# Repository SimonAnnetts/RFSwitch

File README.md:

# RFSwitch

A 4-way RF switch (one input, four selectable outputs OR four selectable inputs and one output) built from conventional through-hole parts from my parts bin: **J310 JFETs**, a **CD4104-style quad low-to-high voltage level translator**, and a handful of resistors and capacitors.

The RF path is switched at 9–12 V, but the channel-select lines are plain 3.3 V
logic, so the board can be driven directly from a Raspberry Pi Pico W (or any
3.3 V source).

* KiCad project: [RFSwitch/RFSwitch.kicad_pro](RFSwitch/RFSwitch.kicad_pro)
* Schematic: [RFSwitch/RFSwitch.kicad_sch](RFSwitch/RFSwitch.kicad_sch)
* PCB: [RFSwitch/RFSwitch.kicad_pcb](RFSwitch/RFSwitch.kicad_pcb)
* Symbols, footprints and 3D models used by the project are in `RFSwitch/libs` and `RFSwitch/packages3D`.

The switch should work at least up to 75Mhz, and probably well into the VHF range, but I have not tested it yet.

10 PCBs were ordered from JLCPCB in November 2026 costing about GBP 5.00 in total with shipping included. The boards are 50 mm × 50 mm, two-layer, ENIG finish, with a solder mask and silkscreen. I await their arrival, and once I have built and tested one, I will update this README with measured performance figures.

## Interfaces

### Control header J1 (1x8, 2.54 mm)

| Pin | Signal     | Description                                              |
|-----|------------|----------------------------------------------------------|
| 1   | GND        | Ground                                                   |
| 2   | VCC        | 9–12 V supply for the FET bias and switching             |
| 3   | +3V3       | 3.3 V logic supply (from the Pico's 3V3 out)             |
| 4   | EN         | Enables the level-shifter outputs                        |
| 5   | RF1_SEL    | Select channel 1 (3.3 V logic)                           |
| 6   | RF2_SEL    | Select channel 2                                         |
| 7   | RF3_SEL    | Select channel 3                                         |
| 8   | RF4_SEL    | Select channel 4                                         |

### RF connectors

Five edge-mount SMA connectors: `RFIN` (common) and `RFOUT1` … `RFOUT4`.

## How it works

### 1. Signal path

```
                       RF5 (common node, DC-biased to VCC via R18 10k)
                        │
 RFIN ──L1──C4(100n)────┤
                        ├── Q1 (series J310) ── RF1 ──C9(100n)──┬── RFOUT1
                        │                         │             C13 2.2p to GND
                        │                    Q5 (shunt J310)
                        │                         │
                        │                 "Net-(Q5-S)" node ── R19 10k to VCC
                        │                         │             C5..C8 100n to GND
                        ├── Q2 ── RF2 ── (Q6 shunt) ... C10 ── RFOUT2
                        ├── Q3 ── RF3 ── (Q7 shunt) ... C11 ── RFOUT3
                        └── Q4 ── RF4 ── (Q8 shunt) ... C12 ── RFOUT4
```

Each channel has two J310 JFETs:

| Channel | Series FET (common ↔ channel) | Shunt FET (channel ↔ RF ground) |
|---------|-------------------------------|---------------------------------|
| 1       | Q1                            | Q5                              |
| 2       | Q2                            | Q6                              |
| 3       | Q3                            | Q7                              |
| 4       | Q4                            | Q8                              |

* The **series** FET connects the common node `RF5` to the channel node
  (`RF1`…`RF4`). When it is on, the signal passes through; when it is off, the
  channel is disconnected.
* The **shunt** FET connects the channel node to the shunt-source net
  (`Net-(Q5-S)`). That net is held at VCC by R19 (10 k) and decoupled to ground
  by C5–C8 (100 nF), so it is an **RF ground**. When the shunt FET is on it
  shorts any leakage from an unselected channel to ground, which improves
  off-channel isolation.
* `RFIN` reaches the common node through L1 and the DC-blocking capacitor C4;
  each output has its own DC-blocking capacitor (C9–C12, 100 nF).

### 2. Why a J310 can be a switch here

A J310 is a depletion-mode N-channel JFET: with V<sub>GS</sub> = 0 V it is fully
**on** (low channel resistance), and it turns **off** when the gate is taken
several volts below the source (pinch-off is roughly −2 to −6 V).

The schematic takes advantage of this by putting the whole RF path at a **DC
level of VCC**:

* `RF5` is pulled to VCC through R18 (10 k).
* The shunt-source net is pulled to VCC through R19 (10 k).
* Because a channel node is always connected either to `RF5` (series FET on) or
  to the shunt-source net (shunt FET on), every FET source and drain sits at
  about VCC in DC terms.
* The C4 and C9–C12 capacitors block that DC from the connectors.

The FET gates are then driven between **VCC** and **0 V**:

* Gate = VCC → V<sub>GS</sub> = 0 V → FET **on**.
* Gate = 0 V → V<sub>GS</sub> ≈ −VCC (−9 to −12 V) → FET firmly **off**.

Pinching off with the full supply (far beyond pinch-off voltage) keeps the
off-FETs well clear of conduction on RF signal peaks. This is why the board
wants a 9 V or 12 V supply rather than 3.3 V: a 3.3 V gate swing could not
reliably pinch off a J310.

### 3. Level shifting with the 4104

U1 is a quad low-voltage to high-voltage translator with tri-state outputs. It
is supplied from two rails:

| Pin | Name  | Connection                                                   |
|-----|-------|--------------------------------------------------------------|
| 1   | Vddo  | `VCC` (9–12 V) – output side supply                          |
| 16  | Vddi  | `VDDi` – 3.3 V through R1 (1 k), decoupled by C1 (100 nF)    |
| 8   | Vss   | GND                                                          |
| 15  | EN    | `EN` from J1                                                 |

Each of the four sections has one 3.3 V input (`RFn_SEL`) and **two** outputs at
VCC level: a "true" output `RFn_T` and a complementary output `RFn_S`.

| Section | Input (U1 pin) | `_T` output (pin) | `_S` output (pin) |
|---------|----------------|-------------------|-------------------|
| 1       | RF1_SEL (4)    | RF1_T (3)         | RF1_S (2)         |
| 2       | RF2_SEL (12)   | RF2_T (13)        | RF2_S (14)        |
| 3       | RF3_SEL (11)   | RF3_T (10)        | RF3_S (9)         |
| 4       | RF4_SEL (5)    | RF4_T (6)         | RF4_S (7)         |

Each output reaches its FET gate through a 15 k resistor (R10–R17). The `_T`
output drives the **series** FET and the `_S` output drives the **shunt** FET:

| Series FET | Gate net | Shunt FET | Gate net |
|------------|----------|-----------|----------|
| Q1 | RF1_T via R10 | Q5 | RF1_S via R11 |
| Q2 | RF2_T via R12 | Q6 | RF2_S via R13 |
| Q3 | RF3_T via R14 | Q7 | RF3_S via R15 |
| Q4 | RF4_T via R16 | Q8 | RF4_S via R17 |

### 4. Truth table

Because `_T` and `_S` are complementary, a single logic line makes a channel
either "series on / shunt off" or "series off / shunt on":

| RFn_SEL | RFn_T | RFn_S | Series FET | Shunt FET | Channel state |
|---------|-------|-------|------------|-----------|---------------|
| 1 (3.3 V) | VCC | 0 V | on  | off | **Connected** to RFIN |
| 0         | 0 V | VCC | off | on  | **Isolated**, shunted to RF ground |

Normally exactly one `RFn_SEL` should be high at a time. (The hardware does not
enforce this, so setting two high connects two outputs to the input together.)

### 5. Safe state when disabled

Each `_T` line has a 100 k pull-down to ground (R2, R4, R6, R8) and each `_S`
line has a 100 k pull-up to VCC (R3, R5, R7, R9). When the 4104 outputs are
tri-stated (`EN` in the disabling state, or the logic side unpowered) these
resistors define the levels, so **all series FETs turn off and all shunt FETs
turn on**: every output is isolated and shorted to RF ground. The
100 k/15 k values also keep the gates from loading the RF path and slow the
gate edges slightly.

### 6. Power supply decoupling

* C2 (100 nF) – VCC at the connector.
* C3 (100 nF) – VCC at the switch area.
* R1 + C1 – RC filter on the 3.3 V feed into the 4104 `Vddi` pin.

### 7. Other RF components

* **L1 (25–33 nH, 4–5 turns at 3 mm, air-core) in series with C4** at the
  input, and **C13–C16 (2.2 pF) from each output to ground**, are not part of
  the switching mechanism. They are optional frequency-response/impedance
  compensation for the J310 capacitances, and will hopefully allow me to tweak the SWR and insertion loss at VHF. I have not yet tested the board, so I do not know if they are needed or what values are best.

## Bill of materials (summary)

| Ref        | Value                | Function                                      |
|------------|----------------------|-----------------------------------------------|
| Q1–Q4      | J310                 | Series switches                               |
| Q5–Q8      | J310                 | Shunt switches                                |
| U1         | 4104                 | 3.3 V → VCC quad level translator, tri-state  |
| R1         | 1 k                  | `Vddi` series resistor                        |
| R2–R9      | 100 k                | Pull-downs on `_T`, pull-ups on `_S`          |
| R10–R17    | 15 k                 | Gate resistors                                |
| R18, R19   | 10 k                 | DC bias of the common and shunt-source nodes to VCC |
| C1–C3      | 100 nF               | Supply decoupling                             |
| C4         | 100 nF               | Input DC block                                |
| C5–C8      | 100 nF               | RF decoupling of the shunt-source node        |
| C9–C12     | 100 nF               | Output DC blocks                              |
| C13–C16    | 2.2 pF               | Output shunt capacitors                       |
| L1         | 25–33 nH             | Input series inductor (air-core)              |
| J1         | 1x8 pin header       | Power and control                             |
| 5 × SMA    | edge mount           | RFIN, RFOUT1–4                                |

## Usage

1. Connect GND, a 9–12 V supply to VCC, and 3.3 V to +3V3 (J1 pins 1–3).
2. Drive `EN` to the enabling level.
3. Take one `RFn_SEL` line high to route `RFIN` to `RFOUTn`; take it low to
   isolate that channel.

## Notes and caveats

* The schematic was analysed by reading the KiCad files, not by simulation or
  measurement. No bandwidth, insertion-loss or isolation figures are claimed.
* Check the 4104 datasheet to confirm which logic level of `EN` enables the
  outputs and which output pin is the true/complement for each section; the
  description above is derived from how the board is wired.
* Respect the 4104's maximum supply voltage and keep VCC above the J310's
  pinch-off voltage.

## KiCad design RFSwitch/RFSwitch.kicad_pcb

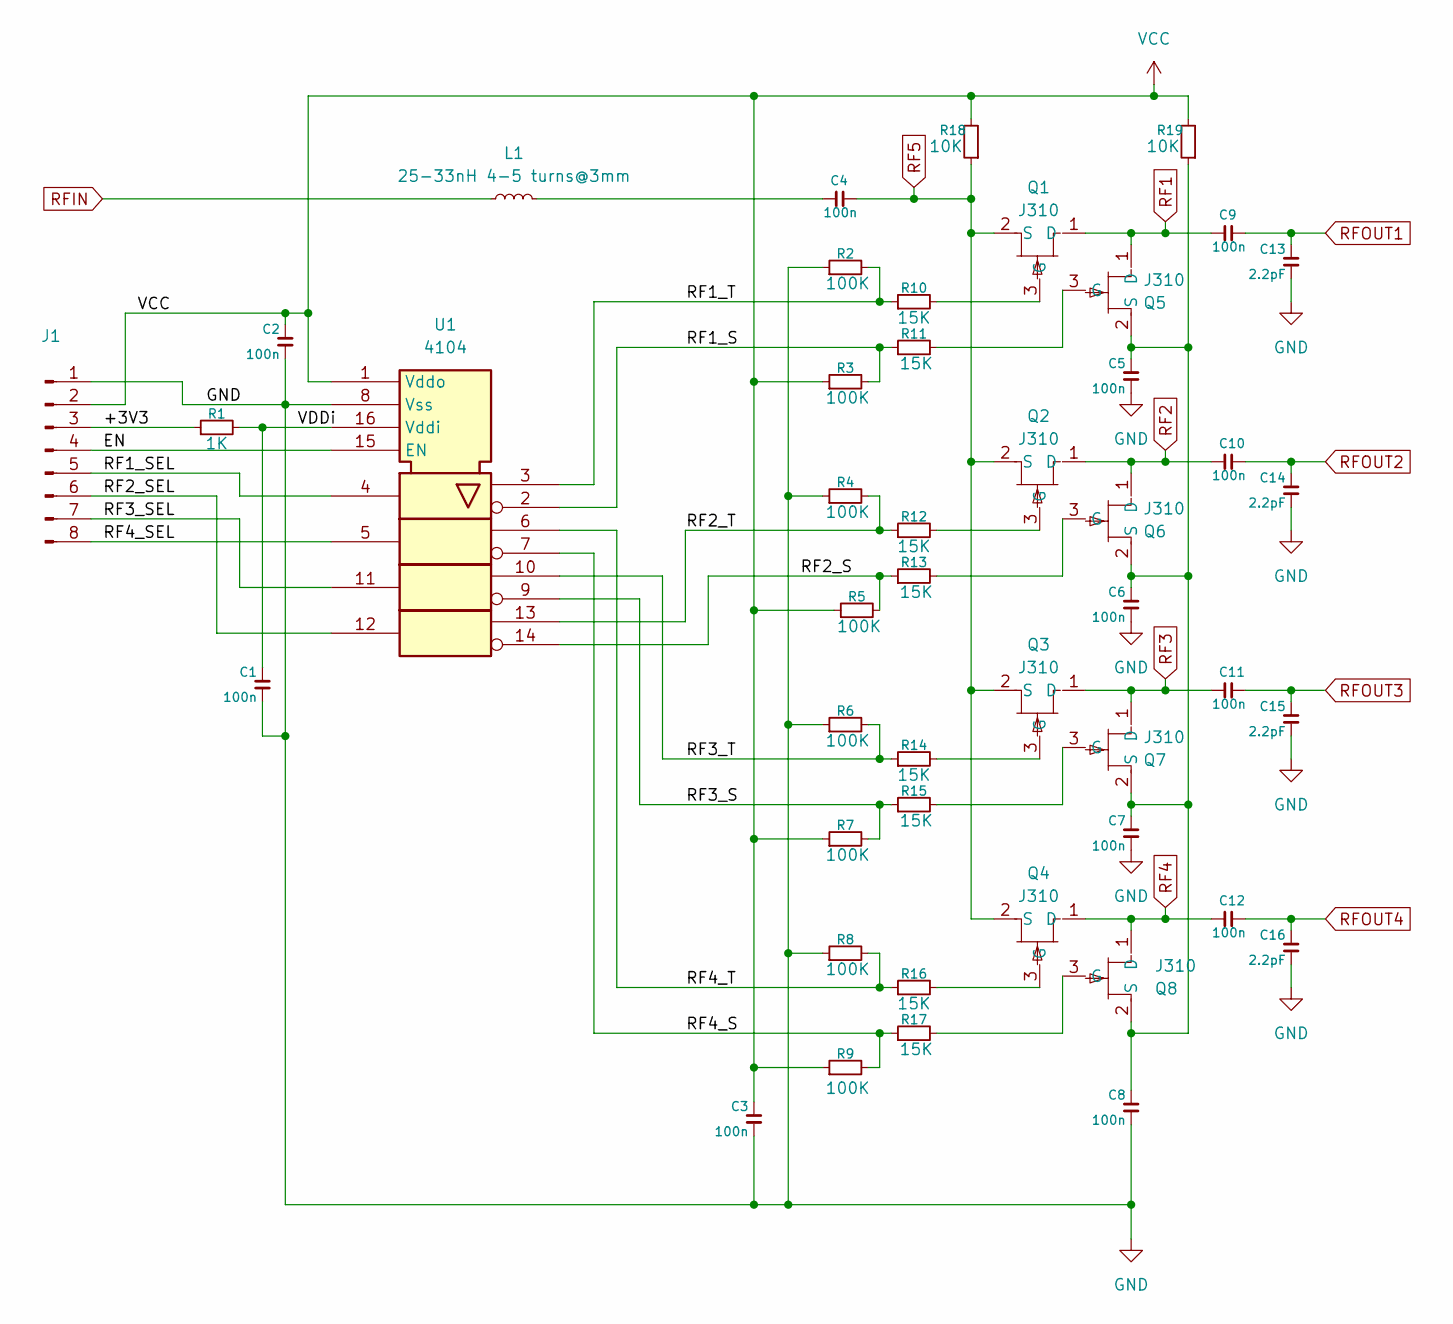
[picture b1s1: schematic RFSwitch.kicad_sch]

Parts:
C1, C2, C3, C4, C5, C6, C7, C8, C9, C10, C11, C12: 100n; C_Disc_D7.0mm_W2.5mm_P5.00mm
C13, C14, C15, C16: 2.2pF; C_Disc_D7.0mm_W2.5mm_P5.00mm
J1: PinHeader_1x08_P2.54mm_Vertical
L1: 25-33nH 4-5 turns@3mm; L_Radial_L7.5mm_W4.6mm_P5.00mm_Neosid_SD75
Q1, Q2, Q3, Q4, Q5, Q6, Q7, Q8: J310; TO-92L_Inline_Wide; MPN J310
R1: 1K; R_Axial_DIN0204_L3.6mm_D1.6mm_P7.62mm_Horizontal
R2, R3, R8, R9: 100K; R_Axial_DIN0204_L3.6mm_D1.6mm_P7.62mm_Horizontal
R4, R5, R6, R7: 100K; R_Axial_DIN0204_L3.6mm_D1.6mm_P2.54mm_Vertical
R10, R12, R14, R16: 15K; R_Axial_DIN0204_L3.6mm_D1.6mm_P2.54mm_Vertical
R11, R13, R15, R17: 15K; R_Axial_DIN0204_L3.6mm_D1.6mm_P7.62mm_Horizontal
R18, R19: 10K; R_Axial_DIN0204_L3.6mm_D1.6mm_P7.62mm_Horizontal
U1: 4104; DIP-16_W7.62mm_Socket

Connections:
/+3V3: J1.3, R1.1
/EN: J1.4, U1.15 (EN)
/RF1_S: R3.2, R11.1, U1.2
/RF1_SEL: J1.5, U1.4
/RF1_T: R2.2, R10.1, U1.3
/RF2_S: R5.2, R13.1, U1.14
/RF2_SEL: J1.6, U1.12
/RF2_T: R4.2, R12.1, U1.13
/RF3_S: R7.2, R15.1, U1.9
/RF3_SEL: J1.7, U1.11
/RF3_T: R6.2, R14.1, U1.10
/RF4_S: R9.2, R17.1, U1.7
/RF4_SEL: J1.8, U1.5
/RF4_T: R8.2, R16.1, U1.6
/VDDi: C1.1, R1.2, U1.16 (Vddi)
GND: C1.2, C2.2, C3.2, C5.2, C6.2, C7.2, C8.2, C13.2, C14.2, C15.2, C16.2, J1.1, R2.1, R4.1, R6.1, R8.1, U1.8 (Vss)
unnamed: C4.2, L1.2
unnamed: Q1.3 (G), R10.2
unnamed: Q2.3 (G), R12.2
unnamed: Q3.3 (G), R14.2
unnamed: Q4.3 (G), R16.2
unnamed: Q5.3 (G), R11.2
unnamed: C5.1, C6.1, C7.1, C8.1, Q5.2 (S), Q6.2 (S), Q7.2 (S), Q8.2 (S), R19.1
unnamed: Q6.3 (G), R13.2
unnamed: Q7.3 (G), R15.2
unnamed: Q8.3 (G), R17.2
RF1: C9.2, Q1.1 (D), Q5.1 (D)
RF2: C10.2, Q2.1 (D), Q6.1 (D)
RF3: C11.2, Q3.1 (D), Q7.1 (D)
RF4: C12.2, Q4.1 (D), Q8.1 (D)
RF5: C4.1, Q1.2 (S), Q2.2 (S), Q3.2 (S), Q4.2 (S), R18.1
RFIN: L1.1; also elsewhere on the board
RFOUT1: C9.1, C13.1; also elsewhere on the board
RFOUT2: C10.1, C14.1; also elsewhere on the board
RFOUT3: C11.1, C15.1; also elsewhere on the board
RFOUT4: C12.1, C16.1; also elsewhere on the board
VCC: C2.1, C3.1, J1.2, R3.1, R5.1, R7.1, R9.1, R18.2, R19.2, U1.1 (Vddo)

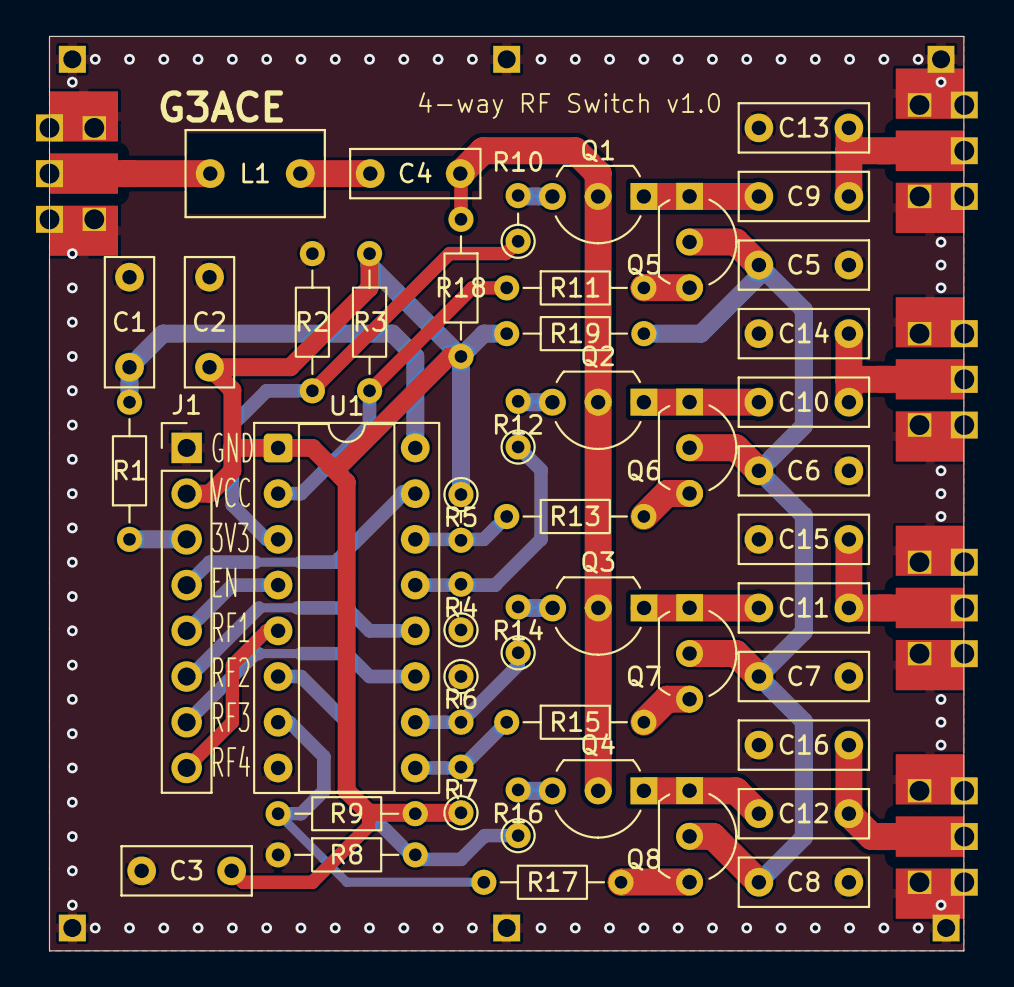
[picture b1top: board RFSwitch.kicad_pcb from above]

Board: 2 copper layers, 50.8 x 50.8 mm, 51 parts (0 on the bottom side), 37 nets.

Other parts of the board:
CP1, CP2, CP2#2, CP2#3, CP2#4: 50R; SMD_TrackEnd_1.5x1.5_mask

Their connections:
RFIN: CP1.1 (50_1); also elsewhere on the board
RFOUT1: CP2#4.1 (50); also elsewhere on the board
RFOUT2: CP2#3.1 (50); also elsewhere on the board
RFOUT3: CP2.1 (50); also elsewhere on the board
RFOUT4: CP2#2.1 (50); also elsewhere on the board

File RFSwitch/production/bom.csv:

Designator,Footprint,Quantity,Value,LCSC Part #
"C1, C10, C11, C12, C2, C3, C4, C5, C6, C7, C8, C9",C_Disc_D7.0mm_W2.5mm_P5.00mm,12,100n,
"C13, C14, C15, C16",C_Disc_D7.0mm_W2.5mm_P5.00mm,4,2.2pF,
J1,PinHeader_1x08_P2.54mm_Vertical,1,~,
L1,L_Radial_L7.5mm_W4.6mm_P5.00mm_Neosid_SD75,1,25-33nH 4-5 turns@3mm,
"Q1, Q2, Q3, Q4, Q5, Q6, Q7, Q8",TO-92L_Inline_Wide,8,J310,J310
R1,R_Axial_DIN0204_L3.6mm_D1.6mm_P7.62mm_Horizontal,1,1K,
"R10, R12, R14, R16",R_Axial_DIN0204_L3.6mm_D1.6mm_P2.54mm_Vertical,4,15K,
"R11, R13, R15, R17",R_Axial_DIN0204_L3.6mm_D1.6mm_P7.62mm_Horizontal,4,15K,
"R18, R19",R_Axial_DIN0204_L3.6mm_D1.6mm_P7.62mm_Horizontal,2,10K,
"R2, R3, R8, R9",R_Axial_DIN0204_L3.6mm_D1.6mm_P7.62mm_Horizontal,4,100K,
"R4, R5, R6, R7",R_Axial_DIN0204_L3.6mm_D1.6mm_P2.54mm_Vertical,4,100K,
U1,DIP-16_W7.62mm_Socket,1,4104,
